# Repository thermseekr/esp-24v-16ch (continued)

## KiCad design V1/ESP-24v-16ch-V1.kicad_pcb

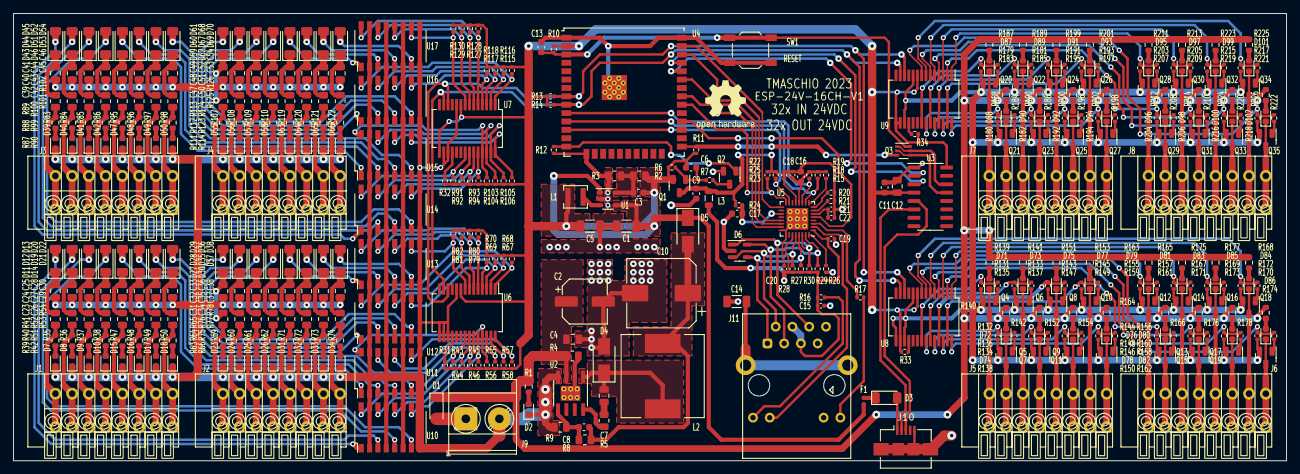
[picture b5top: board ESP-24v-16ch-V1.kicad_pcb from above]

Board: 2 copper layers, 193.0 x 67.8 mm, 450 parts (0 on the bottom side), 348 nets.

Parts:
C1, C5: 10uF/50V/1206; C_1206_3216Metric
C2: 47uF/35V/6,3x5,4; CP_Elec_6.3x5.4
C3: 22pF/50V/0603; C_0603_1608Metric
C4, C7, C12: 0,1uF/50V/0805; C_0805_2012Metric
C6, C9, C11, C16, C17: 10uF/10V/0603; C_0603_1608Metric
C8: 12pF/50V/0603; C_0603_1608Metric
C10: 470uF/16V/10x10; CP_Elec_10x10
C13: 1uF/50V/0603; C_0603_1608Metric
C14: 1nF/2kV/1206; C_1206_3216Metric
C15, C18, C19, C20: 0,1uF/50V/0402; C_0402_1005Metric
C21: 1uF/25V/0402; C_0402_1005Metric
C22: 470pF/50V/0402; C_0402_1005Metric
C23, C24, C25, C26, C27, C28, C29, C30, C31, C32, C33, C34, C35, C36, C37, C38, C39, C40, C41, C42, C43, C44, C45, C46, C47, C48, C49, C50, C51, C52, C53, C54: 33nF/50V/0805; C_0805_2012Metric
D1: SM4007PL/SOD-123; D_SOD-123
D2, D7, D8, D9, D10, D15, D16, D17, D18, D23, D24, D25, D26, D31, D32, D33, D34, D39, D40, D41, D42, D47, D48, D49, D50, D55, D56, D57, D58, D63, D64, D65, D66, D71, D72, D73, D74, D75, D76, D77, D78, D79, D80, D81, D82, D83, D84, D85, D86, D87, D88, D89, D90, D91, D92, D93, D94, D95, D96, D97, D98, D99, D100, D101, D102: GREEN/0603; LED_0603_1608Metric
D3: B5819W; D_SOD-123
D4: SS510; D_SMA
D5: SS34; D_SMA
D6: ESDS314DBV; SOT-23-5
D11, D12, D13, D14, D19, D20, D21, D22, D27, D28, D29, D30, D35, D36, D37, D38, D43, D44, D45, D46, D51, D52, D53, D54, D59, D60, D61, D62, D67, D68, D69, D70: 9V1/500mW; D_MiniMELF
F1: 500mA; Fuse_0402_1005Metric
J1, J2, J3, J4, J5, J6, J7, J8: Conn_01x08; TerminalBlock_Dorabo_DB141V-2.54-08P_1x08_P2.54mm_Vertical
J9: VIN; TerminalBlock_Phoenix_MKDS-3-2-5.08_1x02_P5.08mm_Horizontal
J10: USB; USB_Micro-B_Amphenol_10104110_Horizontal
J11: ETHERNET; RJ45_HanRun_HR911105A
L1: 2,2uH 1,5A; L_3x3_H1.5
L2: 33uH 2,1A; L_12x12mm_H6mm
L3: 2A 600R; L_0805_2012Metric
Q1: WPM2015-3/TR; SOT-23
Q2: LMUN2211LT1G; SOT-23
Q3: UMH3N; SOT-363_SC-70-6
Q4, Q5, Q6, Q7, Q8, Q9, Q10, Q11, Q12, Q13, Q14, Q15, Q16, Q17, Q18, Q19, Q20, Q21, Q22, Q23, Q24, Q25, Q26, Q27, Q28, Q29, Q30, Q31, Q32, Q33, Q34, Q35: MMBT2222A/SOT-23-3; SOT-23
R1, R35, R36, R37, R38, R47, R48, R49, R50, R59, R60, R61, R62, R71, R72, R73, R74, R83, R84, R85, R86, R95, R96, R97, R98, R107, R108, R109, R110, R119, R120, R121, R122, R139, R140, R141, R142, R151, R152, R153, R154, R163, R164, R165, R166, R175, R176, R177, R178, R187, R188, R189, R190, R199, R200, R201, R202, R211, R212, R213, R214, R223, R224, R225, R226: 5,6k/0,1W/0603; R_0603_1608Metric
R2: 100k/0,125W/0805; R_0805_2012Metric
R3: 22,1k/0,125W/0805; R_0805_2012Metric
R4: 30mR/0,250W/0805; R_0805_2012Metric
R5: 5R1/0,125W/0805; R_0805_2012Metric
R6, R10, R11, R12, R24, R131, R132, R133, R134, R143, R144, R145, R146, R155, R156, R157, R158, R167, R168, R169, R170, R179, R180, R181, R182, R191, R192, R193, R194, R203, R204, R205, R206, R215, R216, R217, R218: 10k/62,5mW/0402; R_0402_1005Metric
R7, R31, R32, R33, R34, R135, R136, R137, R138, R147, R148, R149, R150, R159, R160, R161, R162, R171, R172, R173, R174, R183, R184, R185, R186, R195, R196, R197, R198, R207, R208, R209, R210, R219, R220, R221, R222: 1k/62,5mW/0402; R_0402_1005Metric
R8: 300k/0,125W/0805; R_0805_2012Metric
R9: 52,3k/0,125W/0805; R_0805_2012Metric
R13, R14, R15, R18, R19, R20, R21, R22, R23, R25, R43, R44, R45, R46, R55, R56, R57, R58, R67, R68, R69, R70, R79, R80, R81, R82, R91, R92, R93, R94, R103, R104, R105, R106, R115, R116, R117, R118, R127, R128, R129, R130: 2k2/62,5mW/0402; R_0402_1005Metric
R16, R17: 330R/62,5mW/0402; R_0402_1005Metric
R26: 12,1k/62,5mW/0402; R_0402_1005Metric
R27, R28, R29, R30: 49,9R/62,5mW/0402; R_0402_1005Metric
R39, R40, R41, R42, R51, R52, R53, R54, R63, R64, R65, R66, R75, R76, R77, R78, R87, R88, R89, R90, R99, R100, R101, R102, R111, R112, R113, R114, R123, R124, R125, R126: 1k8/0,125W/0805; R_0805_2012Metric
SW1: RESET; SW_SPST_TL3342
U1: SY8089A1AAC; TSOT-23-5
U2: TX4138; SOIC-8-1EP_3.9x4.9mm_P1.27mm_EP2.29x3mm_ThermalVias
U3: CH340C; SOIC-16_3.9x9.9mm_P1.27mm
U4: ESP32-WROOM-32UE-N16; ESP32-WROOM-32U
U5: LAN8710A; QFN-32-1EP_5x5mm_P0.5mm_EP3.3x3.3mm_ThermalVias
U6, U7, U8, U9: MCP23017_SS; SSOP-28_5.3x10.2mm_P0.65mm
U10, U11, U12, U13, U14, U15, U16, U17: OR-3H4-4; SOP-16_4.4x10.4mm_P1.27mm

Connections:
+3.3V: C3.1, C5.1, C6.1, C11.1, C12.1, L1.2, Q1.2 (S), R2.1, R6.1, R10.1, R11.1, R13.1, R14.1, R31.1, R32.1, R33.1, R34.1, R43.1, R44.1, R45.1, R46.1, R55.1, R56.1, R57.1, R58.1, R67.1, R68.1, R69.1, R70.1, R79.1, R80.1, R81.1, R82.1, R91.1, R92.1, R93.1, R94.1, R103.1, R104.1, R105.1, R106.1, R115.1, R116.1, R117.1, R118.1, R127.1, R128.1, R129.1, R130.1, U3.4 (V3), U3.16 (VCC), U4.2 (VDD), U6.9 (VDD), U7.9 (VDD), U7.15 (A0), U8.9 (VDD), U8.16 (A1), U9.9 (VDD), U9.15 (A0), U9.16 (A1)
+3.3VA: C15.1, C19.1, C20.1, J11.4, J11.5, L3.2, R16.1, R27.2, R28.2, R29.2, R30.2, U5.1 (VDD2A), U5.27 (VDD1A)
+3.3VLAN: C9.1, C16.1, C18.1, L3.1, Q1.3 (D), R15.1, R18.1, R19.1, R22.1, R24.1, R25.1, U5.12 (VDDIO)
+5V: C1.1, D5.1 (K), F1.2, U1.1 (EN), U1.4 (IN)
+24V: C2.1, C4.1, D1.1 (K), R1.1, R4.1, R139.1, R140.1, R141.1, R142.1, R151.1, R152.1, R153.1, R154.1, R163.1, R164.1, R165.1, R166.1, R175.1, R176.1, R177.1, R178.1, R187.1, R188.1, R189.1, R190.1, R199.1, R200.1, R201.1, R202.1, R211.1, R212.1, R213.1, R214.1, R223.1, R224.1, R225.1, R226.1, U2.3 (VIN)
/GPIO Expanders/IN1: R43.2, U6.21 (GPA0), U10.16
/GPIO Expanders/IN2: R44.2, U6.22 (GPA1), U10.14
/GPIO Expanders/IN3: R45.2, U6.23 (GPA2), U10.12
/GPIO Expanders/IN4: R46.2, U6.24 (GPA3), U10.10
/GPIO Expanders/IN5: R55.2, U6.25 (GPA4), U11.16
/GPIO Expanders/IN6: R56.2, U6.26 (GPA5), U11.14
/GPIO Expanders/IN7: R57.2, U6.27 (GPA6), U11.12
/GPIO Expanders/IN8: R58.2, U6.28 (GPA7), U11.10
/GPIO Expanders/IN9: R67.2, U6.1 (GPB0), U12.16
/GPIO Expanders/IN10: R68.2, U6.2 (GPB1), U12.14
/GPIO Expanders/IN11: R69.2, U6.3 (GPB2), U12.12
/GPIO Expanders/IN12: R70.2, U6.4 (GPB3), U12.10
/GPIO Expanders/IN13: R79.2, U6.5 (GPB4), U13.16
/GPIO Expanders/IN14: R80.2, U6.6 (GPB5), U13.14
/GPIO Expanders/IN15: R81.2, U6.7 (GPB6), U13.12
/GPIO Expanders/IN16: R82.2, U6.8 (GPB7), U13.10
/GPIO Expanders/IN17: R91.2, U7.21 (GPA0), U14.16
/GPIO Expanders/IN18: R92.2, U7.22 (GPA1), U14.14
/GPIO Expanders/IN19: R93.2, U7.23 (GPA2), U14.12
/GPIO Expanders/IN20: R94.2, U7.24 (GPA3), U14.10
/GPIO Expanders/IN21: R103.2, U7.25 (GPA4), U15.16
/GPIO Expanders/IN22: R104.2, U7.26 (GPA5), U15.14
/GPIO Expanders/IN23: R105.2, U7.27 (GPA6), U15.12
/GPIO Expanders/IN24: R106.2, U7.28 (GPA7), U15.10
/GPIO Expanders/IN25: R115.2, U7.1 (GPB0), U16.16
/GPIO Expanders/IN26: R116.2, U7.2 (GPB1), U16.14
/GPIO Expanders/IN27: R117.2, U7.3 (GPB2), U16.12
/GPIO Expanders/IN28: R118.2, U7.4 (GPB3), U16.10
/GPIO Expanders/IN29: R127.2, U7.5 (GPB4), U17.16
/GPIO Expanders/IN30: R128.2, U7.6 (GPB5), U17.14
/GPIO Expanders/IN31: R129.2, U7.7 (GPB6), U17.12
/GPIO Expanders/IN32: R130.2, U7.8 (GPB7), U17.10
/GPIO Expanders/OUT1: R131.1, R135.2, U8.21 (GPA0)
/GPIO Expanders/OUT2: R132.1, R136.2, U8.22 (GPA1)
/GPIO Expanders/OUT3: R133.1, R137.2, U8.23 (GPA2)
/GPIO Expanders/OUT4: R134.1, R138.2, U8.24 (GPA3)
/GPIO Expanders/OUT5: R143.1, R147.2, U8.25 (GPA4)
/GPIO Expanders/OUT6: R144.1, R148.2, U8.26 (GPA5)
/GPIO Expanders/OUT7: R145.1, R149.2, U8.27 (GPA6)
/GPIO Expanders/OUT8: R146.1, R150.2, U8.28 (GPA7)
/GPIO Expanders/OUT9: R155.1, R159.2, U8.1 (GPB0)
/GPIO Expanders/OUT10: R156.1, R160.2, U8.2 (GPB1)
/GPIO Expanders/OUT11: R157.1, R161.2, U8.3 (GPB2)
/GPIO Expanders/OUT12: R158.1, R162.2, U8.4 (GPB3)
/GPIO Expanders/OUT13: R167.1, R171.2, U8.5 (GPB4)
/GPIO Expanders/OUT14: R168.1, R172.2, U8.6 (GPB5)
/GPIO Expanders/OUT15: R169.1, R173.2, U8.7 (GPB6)
/GPIO Expanders/OUT16: R170.1, R174.2, U8.8 (GPB7)
/GPIO Expanders/OUT17: R179.1, R183.2, U9.21 (GPA0)
/GPIO Expanders/OUT18: R180.1, R184.2, U9.22 (GPA1)
/GPIO Expanders/OUT19: R181.1, R185.2, U9.23 (GPA2)
/GPIO Expanders/OUT20: R182.1, R186.2, U9.24 (GPA3)
/GPIO Expanders/OUT21: R191.1, R195.2, U9.25 (GPA4)
/GPIO Expanders/OUT22: R192.1, R196.2, U9.26 (GPA5)
/GPIO Expanders/OUT23: R193.1, R197.2, U9.27 (GPA6)
/GPIO Expanders/OUT24: R194.1, R198.2, U9.28 (GPA7)
/GPIO Expanders/OUT25: R203.1, R207.2, U9.1 (GPB0)
/GPIO Expanders/OUT26: R204.1, R208.2, U9.2 (GPB1)
/GPIO Expanders/OUT27: R205.1, R209.2, U9.3 (GPB2)
/GPIO Expanders/OUT28: R206.1, R210.2, U9.4 (GPB3)
/GPIO Expanders/OUT29: R215.1, R219.2, U9.5 (GPB4)
/GPIO Expanders/OUT30: R216.1, R220.2, U9.6 (GPB5)
/GPIO Expanders/OUT31: R217.1, R221.2, U9.7 (GPB6)
/GPIO Expanders/OUT32: R218.1, R222.2, U9.8 (GPB7)
/Inputs 1-16/J4-IN1: J1.1, R35.1, R39.2
/Inputs 1-16/J4-IN2: J1.2, R36.1, R40.2
/Inputs 1-16/J4-IN3: J1.3, R37.1, R41.2
/Inputs 1-16/J4-IN4: J1.4, R38.1, R42.2
/Inputs 1-16/J4-IN5: J1.5, R47.1, R51.2
/Inputs 1-16/J4-IN6: J1.6, R48.1, R52.2
/Inputs 1-16/J4-IN7: J1.7, R49.1, R53.2
/Inputs 1-16/J4-IN8: J1.8, R50.1, R54.2
/Inputs 1-16/J5-IN9: J2.1, R59.1, R63.2
/Inputs 1-16/J5-IN10: J2.2, R60.1, R64.2
/Inputs 1-16/J5-IN11: J2.3, R61.1, R65.2
/Inputs 1-16/J5-IN12: J2.4, R62.1, R66.2
/Inputs 1-16/J5-IN13: J2.5, R71.1, R75.2
/Inputs 1-16/J5-IN14: J2.6, R72.1, R76.2
/Inputs 1-16/J5-IN15: J2.7, R73.1, R77.2
/Inputs 1-16/J5-IN16: J2.8, R74.1, R78.2
/Inputs 17-32/J6-IN17: J3.1, R83.1, R87.2
/Inputs 17-32/J6-IN18: J3.2, R84.1, R88.2
/Inputs 17-32/J6-IN19: J3.3, R85.1, R89.2
/Inputs 17-32/J6-IN20: J3.4, R86.1, R90.2
/Inputs 17-32/J6-IN21: J3.5, R95.1, R99.2
/Inputs 17-32/J6-IN22: J3.6, R96.1, R100.2
/Inputs 17-32/J6-IN23: J3.7, R97.1, R101.2
/Inputs 17-32/J6-IN24: J3.8, R98.1, R102.2
/Inputs 17-32/J7-IN25: J4.1, R107.1, R111.2
/Inputs 17-32/J7-IN26: J4.2, R108.1, R112.2
/Inputs 17-32/J7-IN27: J4.3, R109.1, R113.2
/Inputs 17-32/J7-IN28: J4.4, R110.1, R114.2
/Inputs 17-32/J7-IN29: J4.5, R119.1, R123.2
/Inputs 17-32/J7-IN30: J4.6, R120.1, R124.2
/Inputs 17-32/J7-IN31: J4.7, R121.1, R125.2
/Inputs 17-32/J7-IN32: J4.8, R122.1, R126.2
/LAN/EMAC_CLK: U4.28 (IO17), U5.5 (XTAL1/CLKIN)
/LAN/EMAC_MDC: U4.37 (IO23), U5.17 (MDC)
/LAN/EMAC_MDIO: R22.2, U4.30 (IO18), U5.16 (MDIO)
/LAN/EMAC_RX: R25.2, U4.12 (IO27), U5.15 (COL/CRS_DV/~MODE2)
/LAN/EMAC_RXD0: R19.2, U4.10 (IO25), U5.11 (RXD0/~MODE0)
/LAN/EMAC_RXD1: R18.2, U4.11 (IO26), U5.10 (RXD1/~MODE1)
/LAN/EMAC_TXD0: U4.31 (IO19), U5.22 (TXD0)
/LAN/EMAC_TXD1: U4.36 (IO22), U5.23 (TXD1)
/LAN/EMAC_TXEN: U4.33 (IO21), U5.21 (TXEN)
/LAN/LED_G_K: J11.10, U5.2 (LED2/~INTSEL)
/LAN/LED_Y_A: R17.1, U5.3 (LED1/~REGOFF)
/LAN/RD+: D6.5 (I/04), J11.3 (RD+), R29.1, U5.31 (RXP)
/LAN/RD-: D6.1 (I/01), J11.6 (RD-), R30.1, U5.30 (RXN)
/LAN/TD+: D6.4 (I/03), J11.1 (TD+), R27.1, U5.29 (TXP)
/LAN/TD-: D6.3 (I/02), J11.2 (TD-), R28.1, U5.28 (TXN)
/MCU/I2C_SCL: R13.2, U4.8 (IO32), U6.12 (SCK), U7.12 (SCK), U8.12 (SCK), U9.12 (SCK)
/MCU/I2C_SDA: R14.2, U4.9 (IO33), U6.13 (SDA), U7.13 (SDA), U8.13 (SDA), U9.13 (SDA)
/MCU/PHY_PWR: Q2.1 (B), R12.1, U4.14 (IO12)
/MCU/USB_D+: J10.3 (D+), U3.5 (UD+)
/MCU/USB_D-: J10.2 (D-), U3.6 (UD-)
/Outputs 1-16/J8-OUT1: D71.1 (K), J5.1, Q4.3 (C)
/Outputs 1-16/J8-OUT2: D72.1 (K), J5.2, Q5.3 (C)
/Outputs 1-16/J8-OUT3: D73.1 (K), J5.3, Q6.3 (C)
/Outputs 1-16/J8-OUT4: D74.1 (K), J5.4, Q7.3 (C)
/Outputs 1-16/J8-OUT5: D75.1 (K), J5.5, Q8.3 (C)
/Outputs 1-16/J8-OUT6: D76.1 (K), J5.6, Q9.3 (C)
/Outputs 1-16/J8-OUT7: D77.1 (K), J5.7, Q10.3 (C)
/Outputs 1-16/J8-OUT8: D78.1 (K), J5.8, Q11.3 (C)
/Outputs 1-16/J9-OUT9: D79.1 (K), J6.1, Q12.3 (C)
/Outputs 1-16/J9-OUT10: D80.1 (K), J6.2, Q13.3 (C)
/Outputs 1-16/J9-OUT11: D81.1 (K), J6.3, Q14.3 (C)
/Outputs 1-16/J9-OUT12: D82.1 (K), J6.4, Q15.3 (C)
/Outputs 1-16/J9-OUT13: D83.1 (K), J6.5, Q16.3 (C)
/Outputs 1-16/J9-OUT14: D84.1 (K), J6.6, Q17.3 (C)
/Outputs 1-16/J9-OUT15: D85.1 (K), J6.7, Q18.3 (C)
/Outputs 1-16/J9-OUT16: D86.1 (K), J6.8, Q19.3 (C)
/Outputs 17-32/J10-OUT17: D87.1 (K), J7.1, Q20.3 (C)
/Outputs 17-32/J10-OUT18: D88.1 (K), J7.2, Q21.3 (C)
/Outputs 17-32/J10-OUT19: D89.1 (K), J7.3, Q22.3 (C)
/Outputs 17-32/J10-OUT20: D90.1 (K), J7.4, Q23.3 (C)
/Outputs 17-32/J10-OUT21: D91.1 (K), J7.5, Q24.3 (C)
/Outputs 17-32/J10-OUT22: D92.1 (K), J7.6, Q25.3 (C)
/Outputs 17-32/J10-OUT23: D93.1 (K), J7.7, Q26.3 (C)
/Outputs 17-32/J10-OUT24: D94.1 (K), J7.8, Q27.3 (C)
/Outputs 17-32/J11-OUT25: D95.1 (K), J8.1, Q28.3 (C)
/Outputs 17-32/J11-OUT26: D96.1 (K), J8.2, Q29.3 (C)
/Outputs 17-32/J11-OUT27: D97.1 (K), J8.3, Q30.3 (C)
/Outputs 17-32/J11-OUT28: D98.1 (K), J8.4, Q31.3 (C)
/Outputs 17-32/J11-OUT29: D99.1 (K), J8.5, Q32.3 (C)
/Outputs 17-32/J11-OUT30: D100.1 (K), J8.6, Q33.3 (C)
/Outputs 17-32/J11-OUT31: D101.1 (K), J8.7, Q34.3 (C)
/Outputs 17-32/J11-OUT32: D102.1 (K), J8.8, Q35.3 (C)
GND: C1.2, C2.2, C4.2, C5.2, C9.2, C10.2, C11.2, C12.2, C13.2, C14.2, C15.2, C16.2, C17.2, C18.2, C19.2, C20.2, C21.2, C22.2, C23.2, C24.2, C25.2, C26.2, C27.2, C28.2, C29.2, C30.2, C31.2, C32.2, C33.2, C34.2, C35.2, C36.2, C37.2, C38.2, C39.2, C40.2, C41.2, C42.2, C43.2, C44.2, C45.2, C46.2, C47.2, C48.2, C49.2, C50.2, C51.2, C52.2, C53.2, C54.2, D2.1 (K), D4.2 (A), D6.2 (GND), D7.1 (K), D8.1 (K), D9.1 (K), D10.1 (K), D15.1 (K), D16.1 (K), D17.1 (K), D18.1 (K), D23.1 (K), D24.1 (K), D25.1 (K), D26.1 (K), D31.1 (K), D32.1 (K), D33.1 (K), D34.1 (K), D39.1 (K), D40.1 (K), D41.1 (K), D42.1 (K), D47.1 (K), D48.1 (K), D49.1 (K), D50.1 (K), D55.1 (K), D56.1 (K), D57.1 (K), D58.1 (K), D63.1 (K), D64.1 (K), D65.1 (K), D66.1 (K), J9.2, J10.5 (GND), J10.6 (Shield), J11.8, J11.11, Q2.2 (E), Q4.2 (E), Q5.2 (E), Q6.2 (E), Q7.2 (E), Q8.2 (E), Q9.2 (E), Q10.2 (E), Q11.2 (E), Q12.2 (E), Q13.2 (E), Q14.2 (E), Q15.2 (E), Q16.2 (E), Q17.2 (E), Q18.2 (E), Q19.2 (E), Q20.2 (E), Q21.2 (E), Q22.2 (E), Q23.2 (E), Q24.2 (E), Q25.2 (E), Q26.2 (E), Q27.2 (E), Q28.2 (E), Q29.2 (E), Q30.2 (E), Q31.2 (E), Q32.2 (E), Q33.2 (E), Q34.2 (E), Q35.2 (E), R3.2, R9.2, R12.2, R20.2, R21.2, R23.2, R26.2, R131.2, R132.2, R133.2, R134.2, R143.2, R144.2, R145.2, R146.2, R155.2, R156.2, R157.2, R158.2, R167.2, R168.2, R169.2, R170.2, R179.2, R180.2, R181.2, R182.2, R191.2, R192.2, R193.2, R194.2, R203.2, R204.2, R205.2, R206.2, R215.2, R216.2, R217.2, R218.2, SW1.1, U1.2 (GND), U2.4 (GND), U3.1 (GND), U4.1 (GND), U4.15 (GND), U4.38 (GND), U4.39 (GND), U5.24 (TXD2), U5.25 (TXD3), U5.33 (VSS), U6.10 (VSS), U6.15 (A0), U6.16 (A1), U6.17 (A2), U7.10 (VSS), U7.16 (A1), U7.17 (A2), U8.10 (VSS), U8.15 (A0), U8.17 (A2), U9.10 (VSS), U9.17 (A2), U10.2, U10.4, U10.6, U10.8, U10.9, U10.11, U10.13, U10.15, U11.2, U11.4, U11.6, U11.8, U11.9, U11.11, U11.13, U11.15, U12.2, U12.4, U12.6, U12.8, U12.9, U12.11, U12.13, U12.15, U13.2, U13.4, U13.6, U13.8, U13.9, U13.11, U13.13, U13.15, U14.2, U14.4, U14.6, U14.8, U14.9, U14.11, U14.13, U14.15, U15.2, U15.4, U15.6, U15.8, U15.9, U15.11, U15.13, U15.15, U16.2, U16.4, U16.6, U16.8, U16.9, U16.11, U16.13, U16.15, U17.2, U17.4, U17.6, U17.8, U17.9, U17.11, U17.13, U17.15
unnamed: C21.1, C22.1, U5.6 (VDDCR)
unnamed: C7.1, R5.1
unnamed: C14.1, J11.SH
unnamed: D1.2 (A), J9.1
unnamed: D2.2 (A), R1.2
unnamed: D3.2 (A), J10.1 (VBUS)
unnamed: D3.1 (K), F1.1
unnamed: C7.2, D4.1 (K), L2.1, U2.1 (SW)
unnamed: C8.1, C10.1, D5.2 (A), L2.2, R8.1
unnamed: D7.2 (A), R35.2
unnamed: D8.2 (A), R36.2
unnamed: D9.2 (A), R37.2
unnamed: D10.2 (A), R38.2
unnamed: D11.2 (A), U10.1
unnamed: C23.1, D11.1 (K), R39.1
unnamed: D12.2 (A), U10.3
unnamed: C24.1, D12.1 (K), R40.1
unnamed: D13.2 (A), U10.5
unnamed: C25.1, D13.1 (K), R41.1
unnamed: D14.2 (A), U10.7
unnamed: C26.1, D14.1 (K), R42.1
unnamed: D15.2 (A), R47.2
unnamed: D16.2 (A), R48.2
unnamed: D17.2 (A), R49.2
unnamed: D18.2 (A), R50.2
unnamed: D19.2 (A), U11.1
unnamed: C27.1, D19.1 (K), R51.1
unnamed: D20.2 (A), U11.3
unnamed: C28.1, D20.1 (K), R52.1
unnamed: D21.2 (A), U11.5
unnamed: C29.1, D21.1 (K), R53.1
unnamed: D22.2 (A), U11.7
unnamed: C30.1, D22.1 (K), R54.1
unnamed: D23.2 (A), R59.2
unnamed: D24.2 (A), R60.2
unnamed: D25.2 (A), R61.2
unnamed: D26.2 (A), R62.2
unnamed: D27.2 (A), U12.1
unnamed: C31.1, D27.1 (K), R63.1
unnamed: D28.2 (A), U12.3
unnamed: C32.1, D28.1 (K), R64.1
unnamed: D29.2 (A), U12.5
unnamed: C33.1, D29.1 (K), R65.1
unnamed: D30.2 (A), U12.7
unnamed: C34.1, D30.1 (K), R66.1
unnamed: D31.2 (A), R71.2
unnamed: D32.2 (A), R72.2
unnamed: D33.2 (A), R73.2
unnamed: D34.2 (A), R74.2
unnamed: D35.2 (A), U13.1
unnamed: C35.1, D35.1 (K), R75.1
unnamed: D36.2 (A), U13.3
unnamed: C36.1, D36.1 (K), R76.1
unnamed: D37.2 (A), U13.5
unnamed: C37.1, D37.1 (K), R77.1
unnamed: D38.2 (A), U13.7
unnamed: C38.1, D38.1 (K), R78.1
unnamed: D39.2 (A), R83.2
unnamed: D40.2 (A), R84.2
unnamed: D41.2 (A), R85.2
unnamed: D42.2 (A), R86.2
unnamed: D43.2 (A), U14.1
unnamed: C39.1, D43.1 (K), R87.1
unnamed: D44.2 (A), U14.3
unnamed: C40.1, D44.1 (K), R88.1
unnamed: D45.2 (A), U14.5
unnamed: C41.1, D45.1 (K), R89.1
unnamed: D46.2 (A), U14.7
unnamed: C42.1, D46.1 (K), R90.1
unnamed: D47.2 (A), R95.2
unnamed: D48.2 (A), R96.2
unnamed: D49.2 (A), R97.2
unnamed: D50.2 (A), R98.2
unnamed: D51.2 (A), U15.1
unnamed: C43.1, D51.1 (K), R99.1
unnamed: D52.2 (A), U15.3
unnamed: C44.1, D52.1 (K), R100.1
unnamed: D53.2 (A), U15.5
unnamed: C45.1, D53.1 (K), R101.1
unnamed: D54.2 (A), U15.7
unnamed: C46.1, D54.1 (K), R102.1
unnamed: D55.2 (A), R107.2
unnamed: D56.2 (A), R108.2
unnamed: D57.2 (A), R109.2
unnamed: D58.2 (A), R110.2
unnamed: D59.2 (A), U16.1
unnamed: C47.1, D59.1 (K), R111.1
unnamed: D60.2 (A), U16.3
unnamed: C48.1, D60.1 (K), R112.1
unnamed: D61.2 (A), U16.5
unnamed: C49.1, D61.1 (K), R113.1
unnamed: D62.2 (A), U16.7
unnamed: C50.1, D62.1 (K), R114.1
unnamed: D63.2 (A), R119.2
unnamed: D64.2 (A), R120.2
unnamed: D65.2 (A), R121.2
unnamed: D66.2 (A), R122.2
unnamed: D67.2 (A), U17.1
unnamed: C51.1, D67.1 (K), R123.1
unnamed: D68.2 (A), U17.3
unnamed: C52.1, D68.1 (K), R124.1
unnamed: D69.2 (A), U17.5
unnamed: C53.1, D69.1 (K), R125.1
unnamed: D70.2 (A), U17.7
unnamed: C54.1, D70.1 (K), R126.1
unnamed: D71.2 (A), R139.2
unnamed: D72.2 (A), R140.2
unnamed: D73.2 (A), R141.2
unnamed: D74.2 (A), R142.2
unnamed: D75.2 (A), R151.2
unnamed: D76.2 (A), R152.2
unnamed: D77.2 (A), R153.2
unnamed: D78.2 (A), R154.2
unnamed: D79.2 (A), R163.2
unnamed: D80.2 (A), R164.2
unnamed: D81.2 (A), R165.2
unnamed: D82.2 (A), R166.2
unnamed: D83.2 (A), R175.2
unnamed: D84.2 (A), R176.2
unnamed: D85.2 (A), R177.2
unnamed: D86.2 (A), R178.2
unnamed: D87.2 (A), R187.2
unnamed: D88.2 (A), R188.2
unnamed: D89.2 (A), R189.2
unnamed: D90.2 (A), R190.2
unnamed: D91.2 (A), R199.2
unnamed: D92.2 (A), R200.2
unnamed: D93.2 (A), R201.2
unnamed: D94.2 (A), R202.2
unnamed: D95.2 (A), R211.2
unnamed: D96.2 (A), R212.2
unnamed: D97.2 (A), R213.2
unnamed: D98.2 (A), R214.2
unnamed: D99.2 (A), R223.2
unnamed: D100.2 (A), R224.2
unnamed: D101.2 (A), R225.2
unnamed: D102.2 (A), R226.2
unnamed: J11.9, R16.2
unnamed: J11.12, R17.2
unnamed: C6.2, Q1.1 (G), R6.2, R7.2
unnamed: Q2.3 (C), R7.1
unnamed: Q3.2 (B1), Q3.4 (E2), U3.13 (~DTR)
unnamed: C13.1, Q3.6 (C1), R10.2, SW1.2, U4.3 (EN)
unnamed: Q3.1 (E1), Q3.5 (B2), U3.14 (~RTS)
unnamed: Q3.3 (C2), R11.2, U4.25 (IO0)
unnamed: Q4.1 (B), R135.1
unnamed: Q5.1 (B), R136.1
unnamed: Q6.1 (B), R137.1
unnamed: Q7.1 (B), R138.1
unnamed: Q8.1 (B), R147.1
unnamed: Q9.1 (B), R148.1
unnamed: Q10.1 (B), R149.1
unnamed: Q11.1 (B), R150.1
unnamed: Q12.1 (B), R159.1
unnamed: Q13.1 (B), R160.1
unnamed: Q14.1 (B), R161.1
unnamed: Q15.1 (B), R162.1
unnamed: Q16.1 (B), R171.1
unnamed: Q17.1 (B), R172.1
unnamed: Q18.1 (B), R173.1
unnamed: Q19.1 (B), R174.1
unnamed: Q20.1 (B), R183.1
unnamed: Q21.1 (B), R184.1
unnamed: Q22.1 (B), R185.1
unnamed: Q23.1 (B), R186.1
unnamed: Q24.1 (B), R195.1
unnamed: Q25.1 (B), R196.1
unnamed: Q26.1 (B), R197.1
unnamed: Q27.1 (B), R198.1
unnamed: Q28.1 (B), R207.1
unnamed: Q29.1 (B), R208.1
unnamed: Q30.1 (B), R209.1
unnamed: Q31.1 (B), R210.1
unnamed: Q32.1 (B), R219.1
unnamed: Q33.1 (B), R220.1
unnamed: Q34.1 (B), R221.1
unnamed: Q35.1 (B), R222.1
unnamed: R4.2, U2.2 (ILIM), U2.9 (ILIM)
unnamed: C3.2, R2.2, R3.1, U1.5 (FB)
unnamed: L1.1, U1.3 (LX)
unnamed: R5.2, U2.8 (BS)
unnamed: C8.2, R8.2, R9.1, U2.5 (FB)
unnamed: U3.3 (RXD), U4.35 (TXD0/IO1)
unnamed: U3.2 (TXD), U4.34 (RXD0/IO3)
unnamed: R26.1, U5.32 (RBIAS)
unnamed: R21.1, U5.7 (RXCLK/~PHYAD1)
unnamed: R15.2, U5.9 (RXD2/~RMIISEL)
unnamed: R20.1, U5.8 (RXD3/~PHYAD2)
unnamed: R23.1, U5.13 (RXER/RXD4/~PHYAD0)
unnamed: C17.1, R24.2, U5.19 (~RST)
unnamed: R31.2, U6.18 (~RESET)
unnamed: R32.2, U7.18 (~RESET)
unnamed: R33.2, U8.18 (~RESET)
unnamed: R34.2, U9.18 (~RESET)

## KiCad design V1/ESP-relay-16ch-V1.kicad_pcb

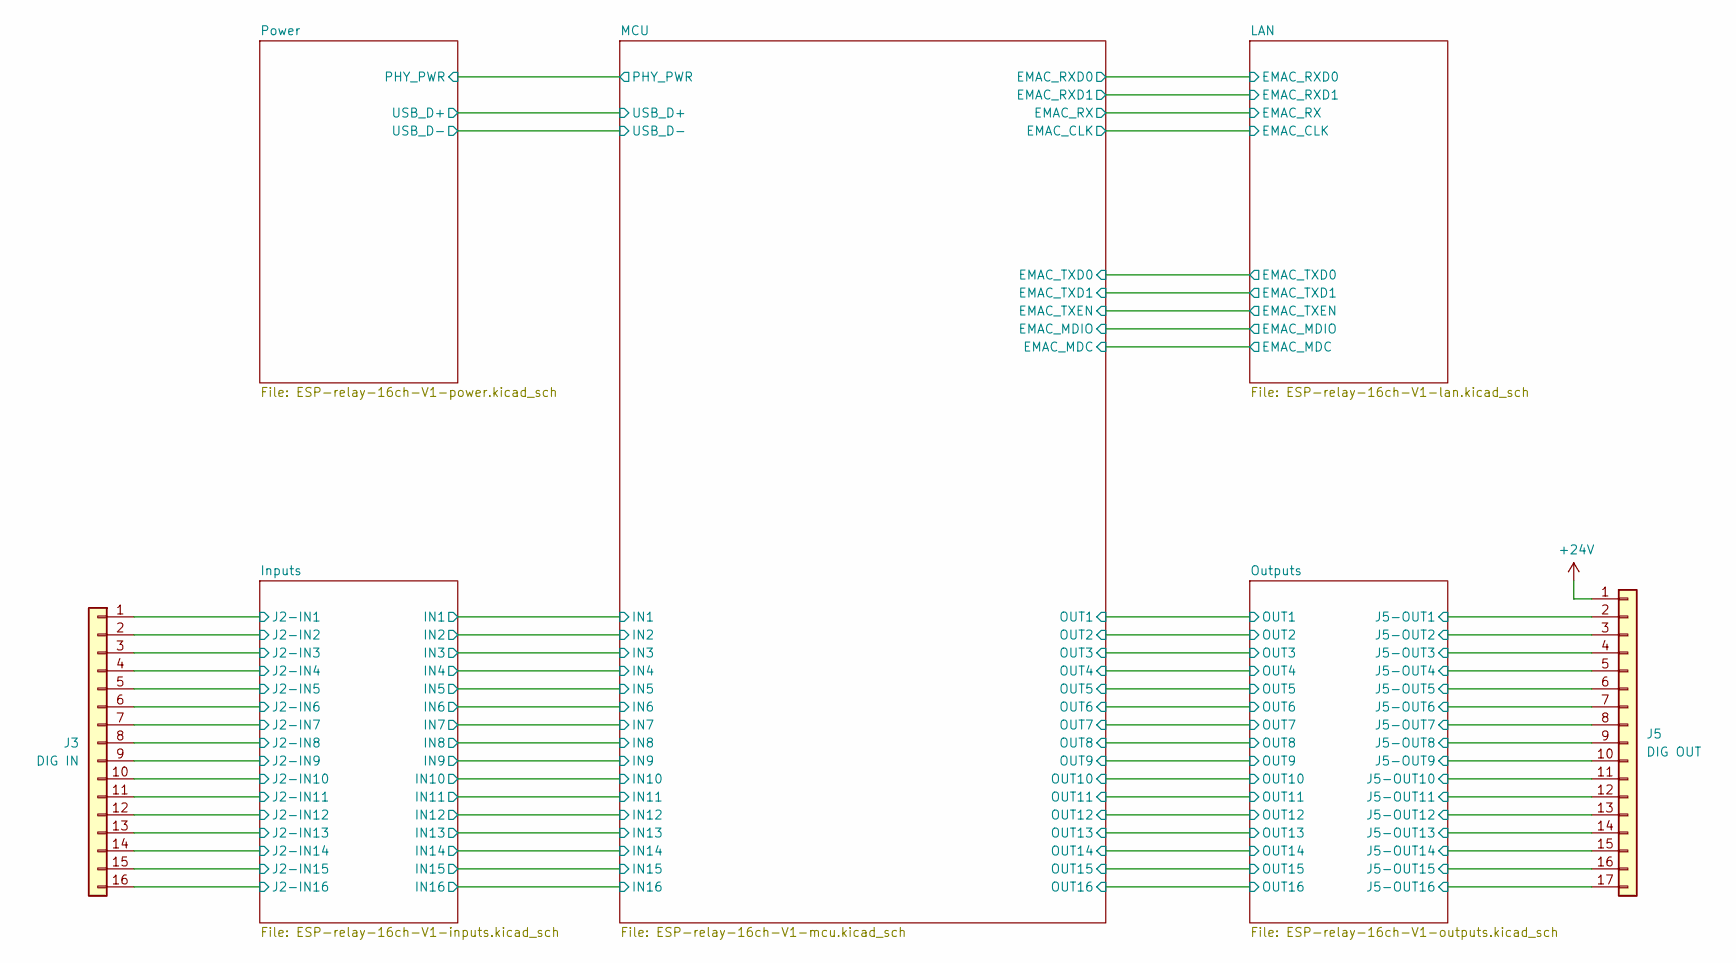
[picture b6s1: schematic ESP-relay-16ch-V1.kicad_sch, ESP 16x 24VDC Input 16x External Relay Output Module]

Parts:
J3: DIG IN; TerminalBlock_Phoenix_PT-1,5-16-3.5-H_1x16_P3.50mm_Horizont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; JLCPCB BOM 0
J5: DIG OUT; TerminalBlock_Phoenix_PT-1,5-17-3.5-H_1x17_P3.50mm_Horizont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; JLCPCB BOM 0

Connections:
+24V: J5.1; also elsewhere on the board
/Inputs/J2-IN1: J3.1; also elsewhere on the board
/Inputs/J2-IN2: J3.2; also elsewhere on the board
/Inputs/J2-IN3: J3.3; also elsewhere on the board
/Inputs/J2-IN4: J3.4; also elsewhere on the board
/Inputs/J2-IN5: J3.5; also elsewhere on the board
/Inputs/J2-IN6: J3.6; also elsewhere on the board
/Inputs/J2-IN7: J3.7; also elsewhere on the board
/Inputs/J2-IN8: J3.8; also elsewhere on the board
/Inputs/J2-IN9: J3.9; also elsewhere on the board
/Inputs/J2-IN10: J3.10; also elsewhere on the board
/Inputs/J2-IN11: J3.11; also elsewhere on the board
/Inputs/J2-IN12: J3.12; also elsewhere on the board
/Inputs/J2-IN13: J3.13; also elsewhere on the board
/Inputs/J2-IN14: J3.14; also elsewhere on the board
/Inputs/J2-IN15: J3.15; also elsewhere on the board
/Inputs/J2-IN16: J3.16; also elsewhere on the board
/Outputs/J5-OUT1: J5.2; also elsewhere on the board
/Outputs/J5-OUT2: J5.3; also elsewhere on the board
/Outputs/J5-OUT3: J5.4; also elsewhere on the board
/Outputs/J5-OUT4: J5.5; also elsewhere on the board
/Outputs/J5-OUT5: J5.6; also elsewhere on the board
/Outputs/J5-OUT6: J5.7; also elsewhere on the board
/Outputs/J5-OUT7: J5.8; also elsewhere on the board
/Outputs/J5-OUT8: J5.9; also elsewhere on the board
/Outputs/J5-OUT9: J5.10; also elsewhere on the board
/Outputs/J5-OUT10: J5.11; also elsewhere on the board
/Outputs/J5-OUT11: J5.12; also elsewhere on the board
/Outputs/J5-OUT12: J5.13; also elsewhere on the board
/Outputs/J5-OUT13: J5.14; also elsewhere on the board
/Outputs/J5-OUT14: J5.15; also elsewhere on the board
/Outputs/J5-OUT15: J5.16; also elsewhere on the board
/Outputs/J5-OUT16: J5.17; also elsewhere on the board

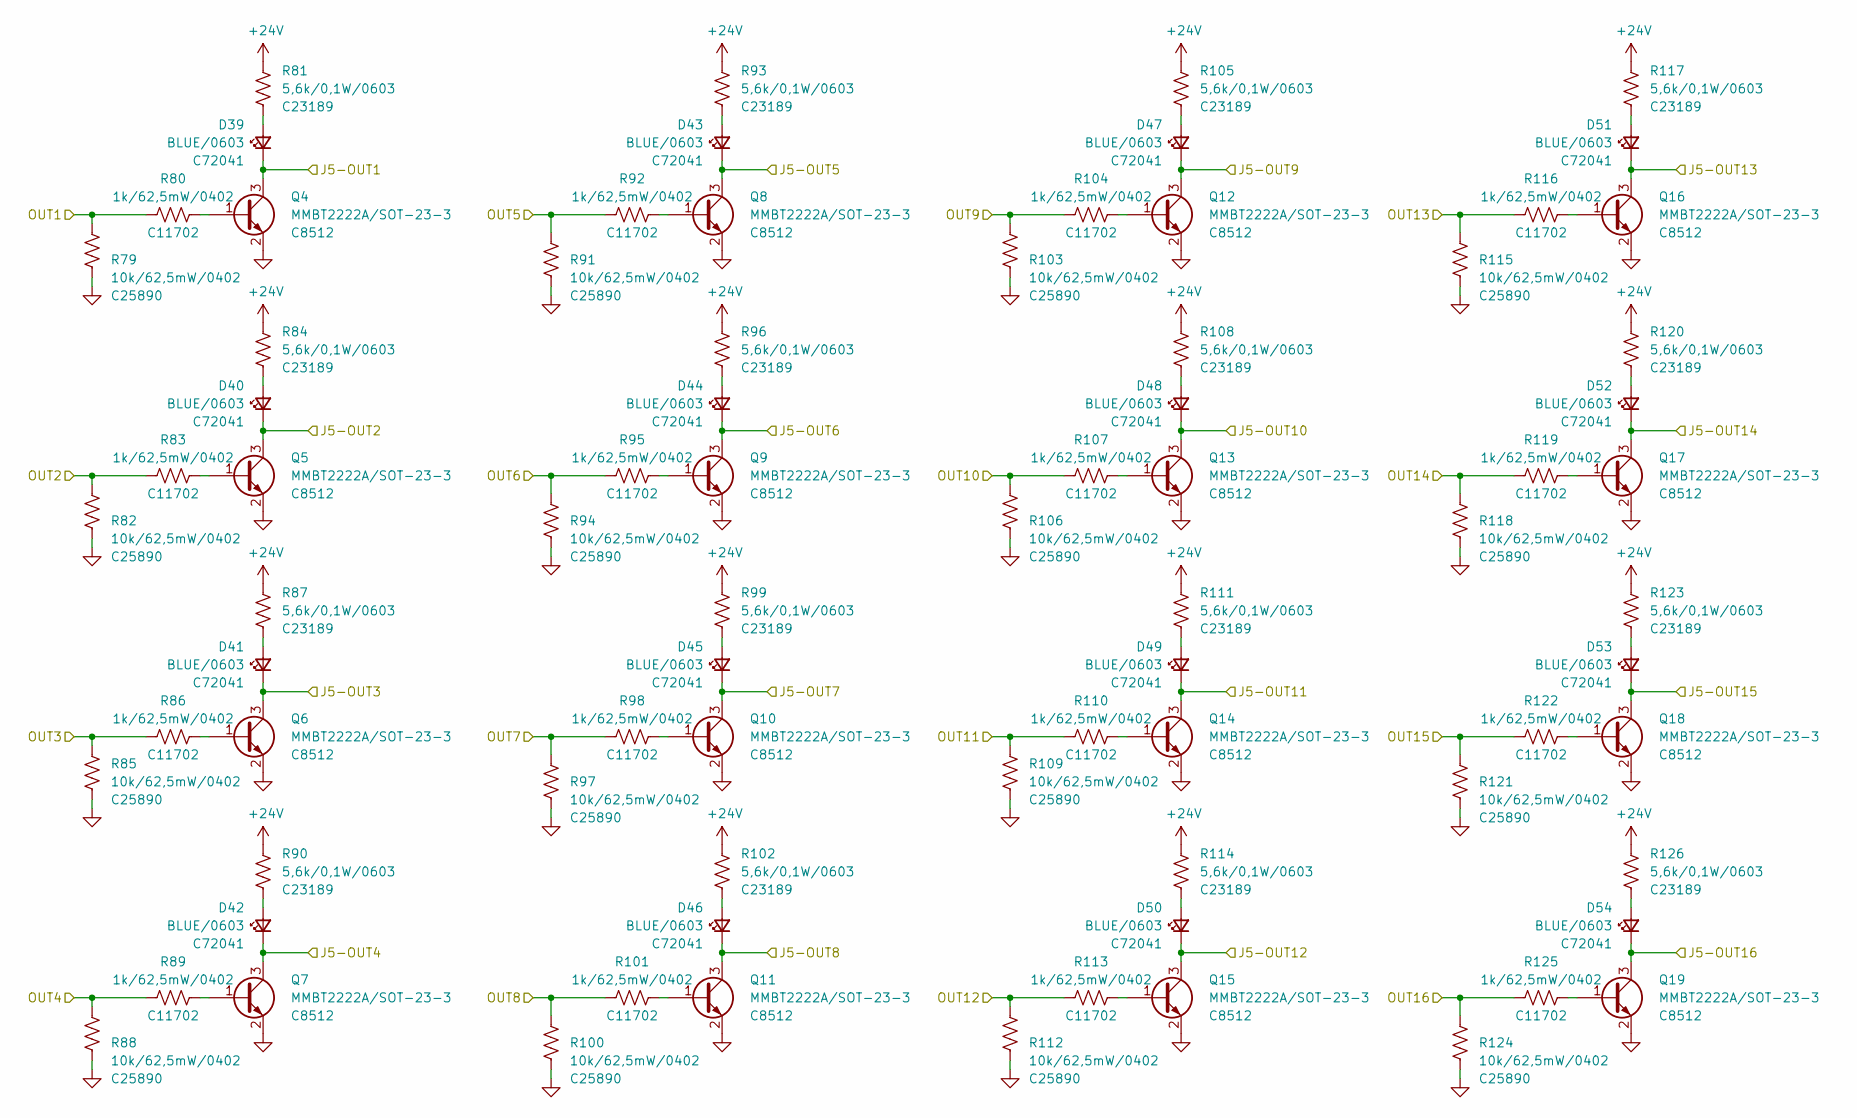
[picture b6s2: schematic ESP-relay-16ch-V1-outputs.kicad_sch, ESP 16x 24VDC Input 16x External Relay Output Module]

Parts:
D39, D40, D41, D42, D43, D44, D45, D46, D47, D48, D49, D50, D51, D52, D53, D54: BLUE/0603; LED_0603_1608Metric; Mfr PN 19-217/BHC-ZL1M2RY/3T; LCSC Part # C72041
Q4, Q5, Q6, Q7, Q8, Q9, Q10, Q11, Q12, Q13, Q14, Q15, Q16, Q17, Q18, Q19: MMBT2222A/SOT-23-3; SOT-23; Mfr PN MMBT2222A; JLCPCB BOM 1
R79, R82, R85, R88, R91, R94, R97, R100, R103, R106, R109, R112, R115, R118, R121, R124: 10k/62,5mW/0402; R_0402_1005Metric; Mfr PN 0402WGF1002TCE; LCSC Part # C25890
R80, R83, R86, R89, R92, R95, R98, R101, R104, R107, R110, R113, R116, R119, R122, R125: 1k/62,5mW/0402; R_0402_1005Metric; Mfr PN 0402WGF1001TCE; LCSC Part # C11702
R81, R84, R87, R90, R93, R96, R99, R102, R105, R108, R111, R114, R117, R120, R123, R126: 5,6k/0,1W/0603; R_0603_1608Metric; Mfr PN 0603WAF5601T5E; LCSC Part # C23189

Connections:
+24V: R81.1, R84.1, R87.1, R90.1, R93.1, R96.1, R99.1, R102.1, R105.1, R108.1, R111.1, R114.1, R117.1, R120.1, R123.1, R126.1; also elsewhere on the board
/MCU/OUT1: R79.1, R80.2; also elsewhere on the board
/MCU/OUT2: R82.1, R83.2; also elsewhere on the board
/MCU/OUT3: R85.1, R86.2; also elsewhere on the board
/MCU/OUT4: R88.1, R89.2; also elsewhere on the board
/MCU/OUT5: R91.1, R92.2; also elsewhere on the board
/MCU/OUT6: R94.1, R95.2; also elsewhere on the board
/MCU/OUT7: R97.1, R98.2; also elsewhere on the board
/MCU/OUT8: R100.1, R101.2; also elsewhere on the board
/MCU/OUT9: R103.1, R104.2; also elsewhere on the board
/MCU/OUT10: R106.1, R107.2; also elsewhere on the board
/MCU/OUT11: R109.1, R110.2; also elsewhere on the board
/MCU/OUT12: R112.1, R113.2; also elsewhere on the board
/MCU/OUT13: R115.1, R116.2; also elsewhere on the board
/MCU/OUT14: R118.1, R119.2; also elsewhere on the board
/MCU/OUT15: R121.1, R122.2; also elsewhere on the board
/MCU/OUT16: R124.1, R125.2; also elsewhere on the board
/Outputs/J5-OUT1: D39.1 (K), Q4.3 (C); also elsewhere on the board
/Outputs/J5-OUT2: D40.1 (K), Q5.3 (C); also elsewhere on the board
/Outputs/J5-OUT3: D41.1 (K), Q6.3 (C); also elsewhere on the board
/Outputs/J5-OUT4: D42.1 (K), Q7.3 (C); also elsewhere on the board
/Outputs/J5-OUT5: D43.1 (K), Q8.3 (C); also elsewhere on the board
/Outputs/J5-OUT6: D44.1 (K), Q9.3 (C); also elsewhere on the board
/Outputs/J5-OUT7: D45.1 (K), Q10.3 (C); also elsewhere on the board
/Outputs/J5-OUT8: D46.1 (K), Q11.3 (C); also elsewhere on the board
/Outputs/J5-OUT9: D47.1 (K), Q12.3 (C); also elsewhere on the board
/Outputs/J5-OUT10: D48.1 (K), Q13.3 (C); also elsewhere on the board
/Outputs/J5-OUT11: D49.1 (K), Q14.3 (C); also elsewhere on the board
/Outputs/J5-OUT12: D50.1 (K), Q15.3 (C); also elsewhere on the board
/Outputs/J5-OUT13: D51.1 (K), Q16.3 (C); also elsewhere on the board
/Outputs/J5-OUT14: D52.1 (K), Q17.3 (C); also elsewhere on the board
/Outputs/J5-OUT15: D53.1 (K), Q18.3 (C); also elsewhere on the board
/Outputs/J5-OUT16: D54.1 (K), Q19.3 (C); also elsewhere on the board
unnamed: D39.2 (A), R81.2
unnamed: D40.2 (A), R84.2
unnamed: D41.2 (A), R87.2
unnamed: D42.2 (A), R90.2
unnamed: D43.2 (A), R93.2
unnamed: D44.2 (A), R96.2
unnamed: D45.2 (A), R99.2
unnamed: D46.2 (A), R102.2
unnamed: D47.2 (A), R105.2
unnamed: D48.2 (A), R108.2
unnamed: D49.2 (A), R111.2
unnamed: D50.2 (A), R114.2
unnamed: D51.2 (A), R117.2
unnamed: D52.2 (A), R120.2
unnamed: D53.2 (A), R123.2
unnamed: D54.2 (A), R126.2
unnamed: Q4.1 (B), R80.1
unnamed: Q5.1 (B), R83.1
unnamed: Q6.1 (B), R86.1
unnamed: Q7.1 (B), R89.1
unnamed: Q8.1 (B), R92.1
unnamed: Q9.1 (B), R95.1
unnamed: Q10.1 (B), R98.1
unnamed: Q11.1 (B), R101.1
unnamed: Q12.1 (B), R104.1
unnamed: Q13.1 (B), R107.1
unnamed: Q14.1 (B), R110.1
unnamed: Q15.1 (B), R113.1
unnamed: Q16.1 (B), R116.1
unnamed: Q17.1 (B), R119.1
unnamed: Q18.1 (B), R122.1
unnamed: Q19.1 (B), R125.1
